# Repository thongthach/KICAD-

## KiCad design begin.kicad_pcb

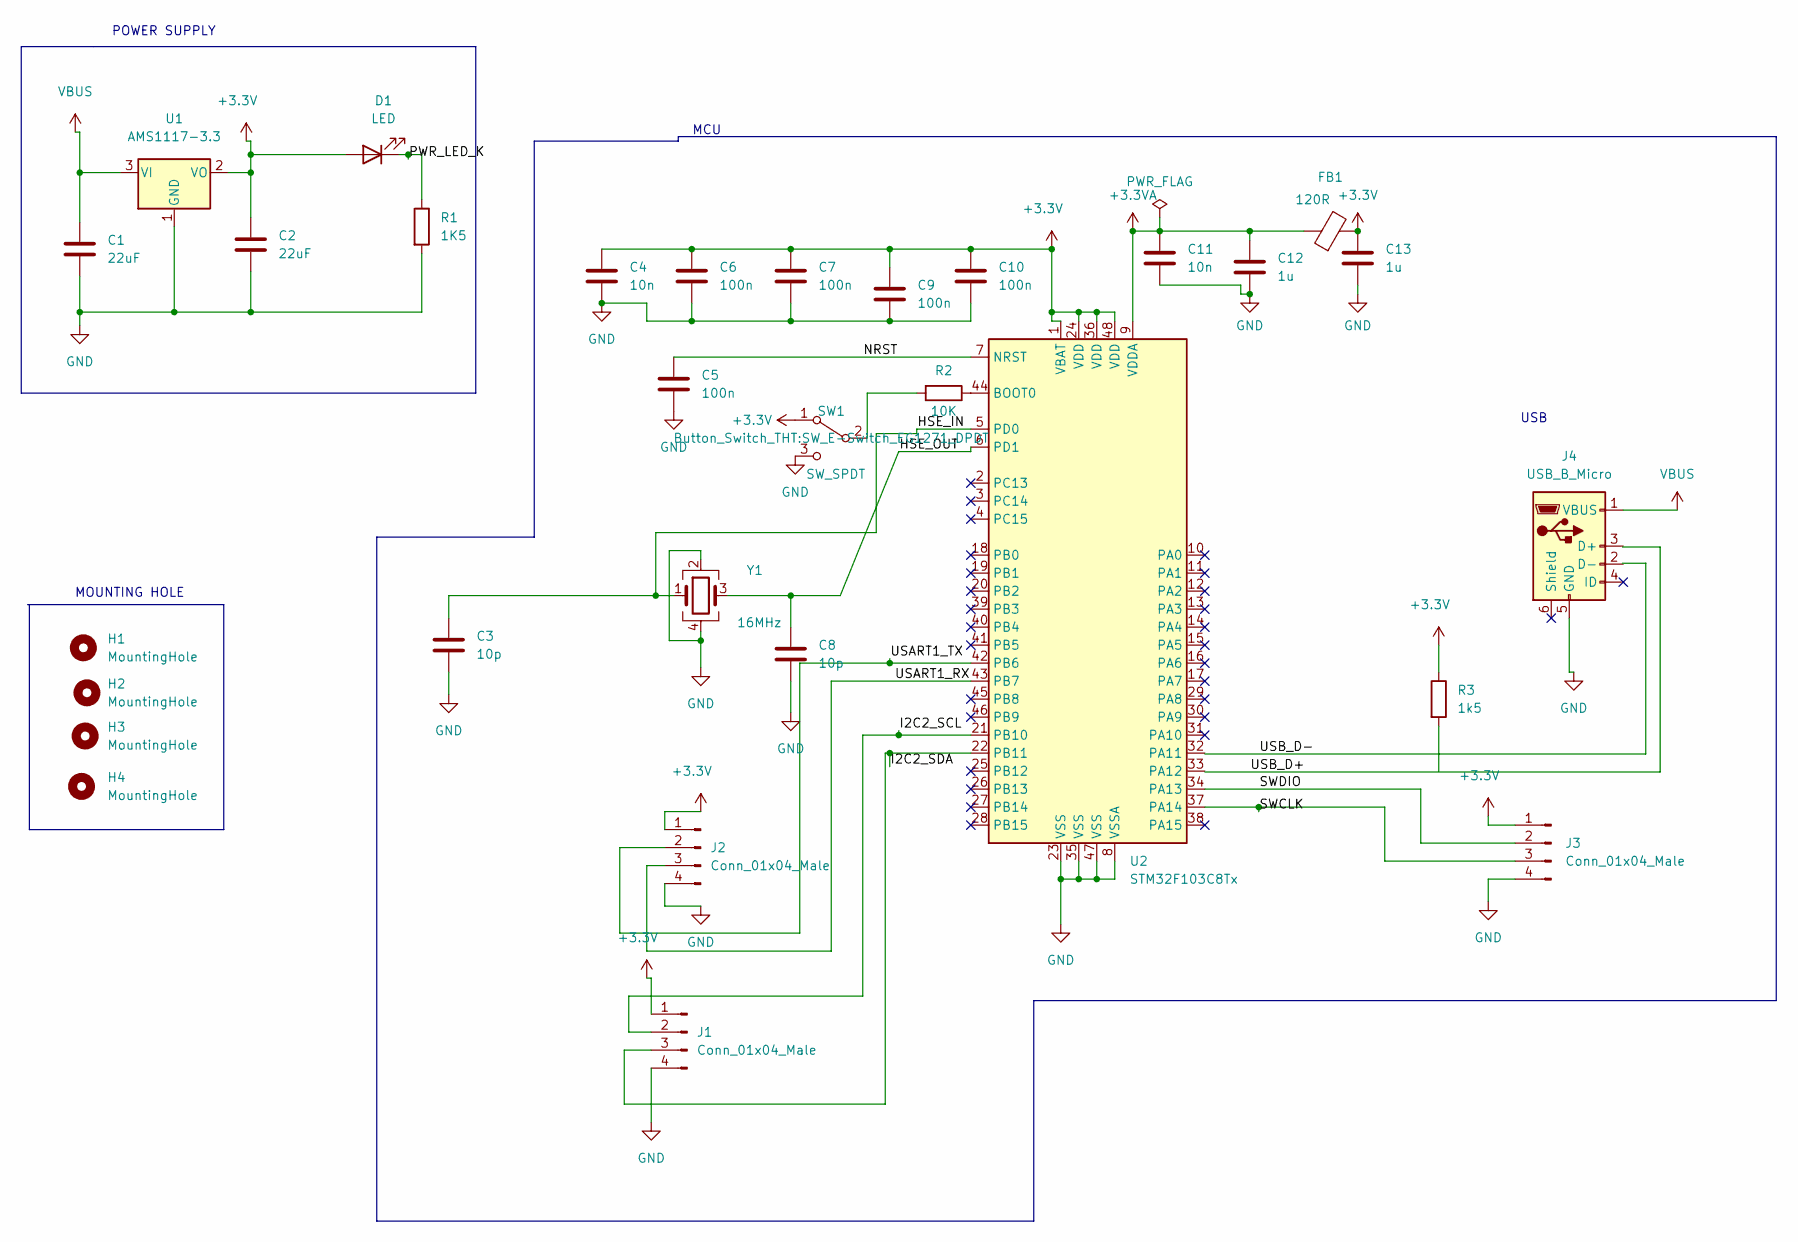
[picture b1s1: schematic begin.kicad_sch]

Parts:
C1, C2: 22uF; C_0805_2012Metric_Pad1.18x1.45mm_HandSolder
C3: 10p; C_0603_1608Metric_Pad1.08x0.95mm_HandSolder
C4: 10n; C_0603_1608Metric_Pad1.08x0.95mm_HandSolder
C5, C6, C7, C9, C10: 100n; C_0402_1005Metric
C8: 10p; C_0402_1005Metric
C11: 10n; C_0402_1005Metric
C12, C13: 1u; C_0402_1005Metric
D1: LED; LED_0603_1608Metric
FB1: 120R; L_0201_0603Metric
H1, H2, H3, H4: MountingHole; MountingHole_2.2mm_M2
J1, J2, J3: Conn_01x04_Male; PinHeader_1x04_P2.00mm_Vertical
J4: USB_B_Micro; USB_Micro-B_Wuerth_629105150521
R1: 1K5; R_0402_1005Metric
R2: 10K; R_0402_1005Metric
R3: 1k5; R_0402_1005Metric
SW1: SW_SPDT; SW_E-Switch_EG1271_DPDT
U1: AMS1117-3.3; SOT-223-3_TabPin2
U2: STM32F103C8Tx; LQFP-48_7x7mm_P0.5mm
Y1: 16MHz; Crystal_SMD_3225-4Pin_3.2x2.5mm

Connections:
+3.3VA: C11.1, C12.1, FB1.1, U2.9 (VDDA)
+3V3: C2.1, C4.1, C6.1, C7.1, C9.1, C10.1, C13.1, D1.2 (A), FB1.2, J1.1, J2.1, J3.1, R3.1, SW1.1 (A), U1.2 (VO), U2.1 (VBAT), U2.24 (VDD), U2.36 (VDD), U2.48 (VDD)
/HSE_IN: C3.1, U2.5 (PD0), Y1.1
/HSE_OUT: C8.1, U2.6 (PD1), Y1.3
/I2C2_SCL: J1.2, U2.21 (PB10)
/I2C2_SDA: J1.3, U2.22 (PB11)
/NRST: C5.1, U2.7 (NRST)
/PWR_LED_K: D1.1 (K), R1.1
/SWCLK: J3.3, U2.37 (PA14)
/SWDIO: J3.2, U2.34 (PA13)
/USART1_RX: J2.3, U2.43 (PB7)
/USART1_TX: J2.2, U2.42 (PB6)
/USB_D+: J4.2 (D-), R3.2, U2.33 (PA12)
/USB_D-: J4.3 (D+), U2.32 (PA11)
GND: C1.2, C2.2, C3.2, C4.2, C5.2, C6.2, C7.2, C8.2, C9.2, C10.2, C11.2, C12.2, C13.2, J1.4, J2.4, J3.4, J4.5 (GND), R1.2, SW1.3 (C), U1.1 (GND), U2.8 (VSSA), U2.23 (VSS), U2.35 (VSS), U2.47 (VSS), Y1.2, Y1.4
unnamed: R2.1, U2.44 (BOOT0)
unnamed: R2.2, SW1.2 (B)
VBUS: C1.1, J4.1 (VBUS), U1.3 (VI)

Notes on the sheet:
MCU
USB
POWER SUPPLY
MOUNTING HOLE

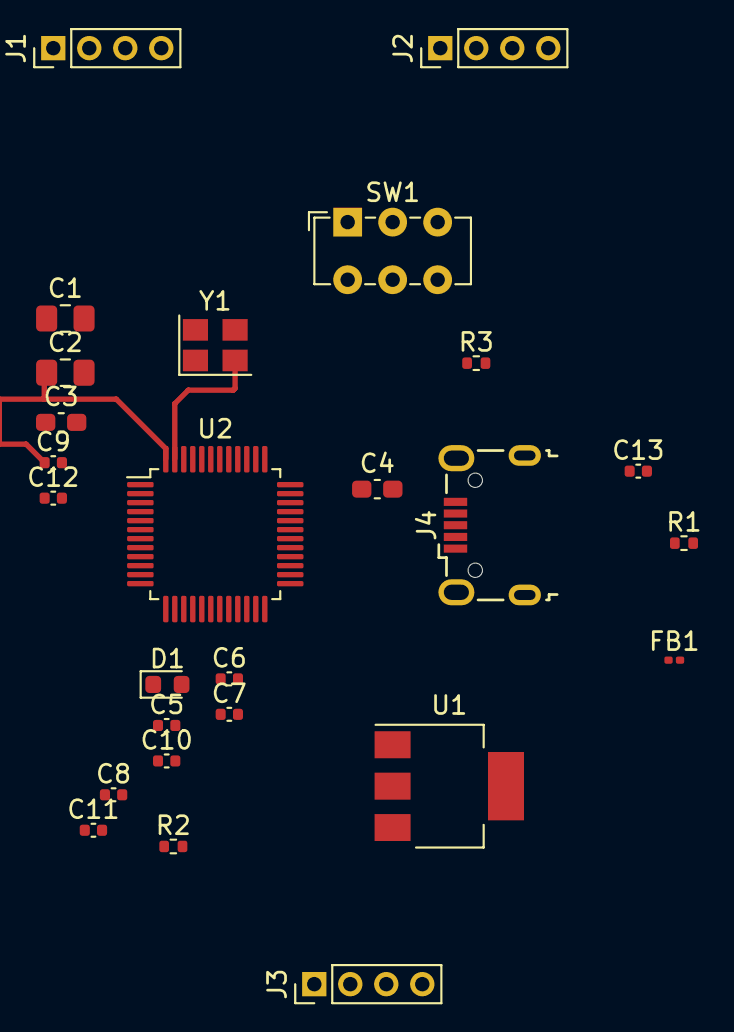
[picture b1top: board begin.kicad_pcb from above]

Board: 2 copper layers, 30 parts (0 on the bottom side), 18 nets.

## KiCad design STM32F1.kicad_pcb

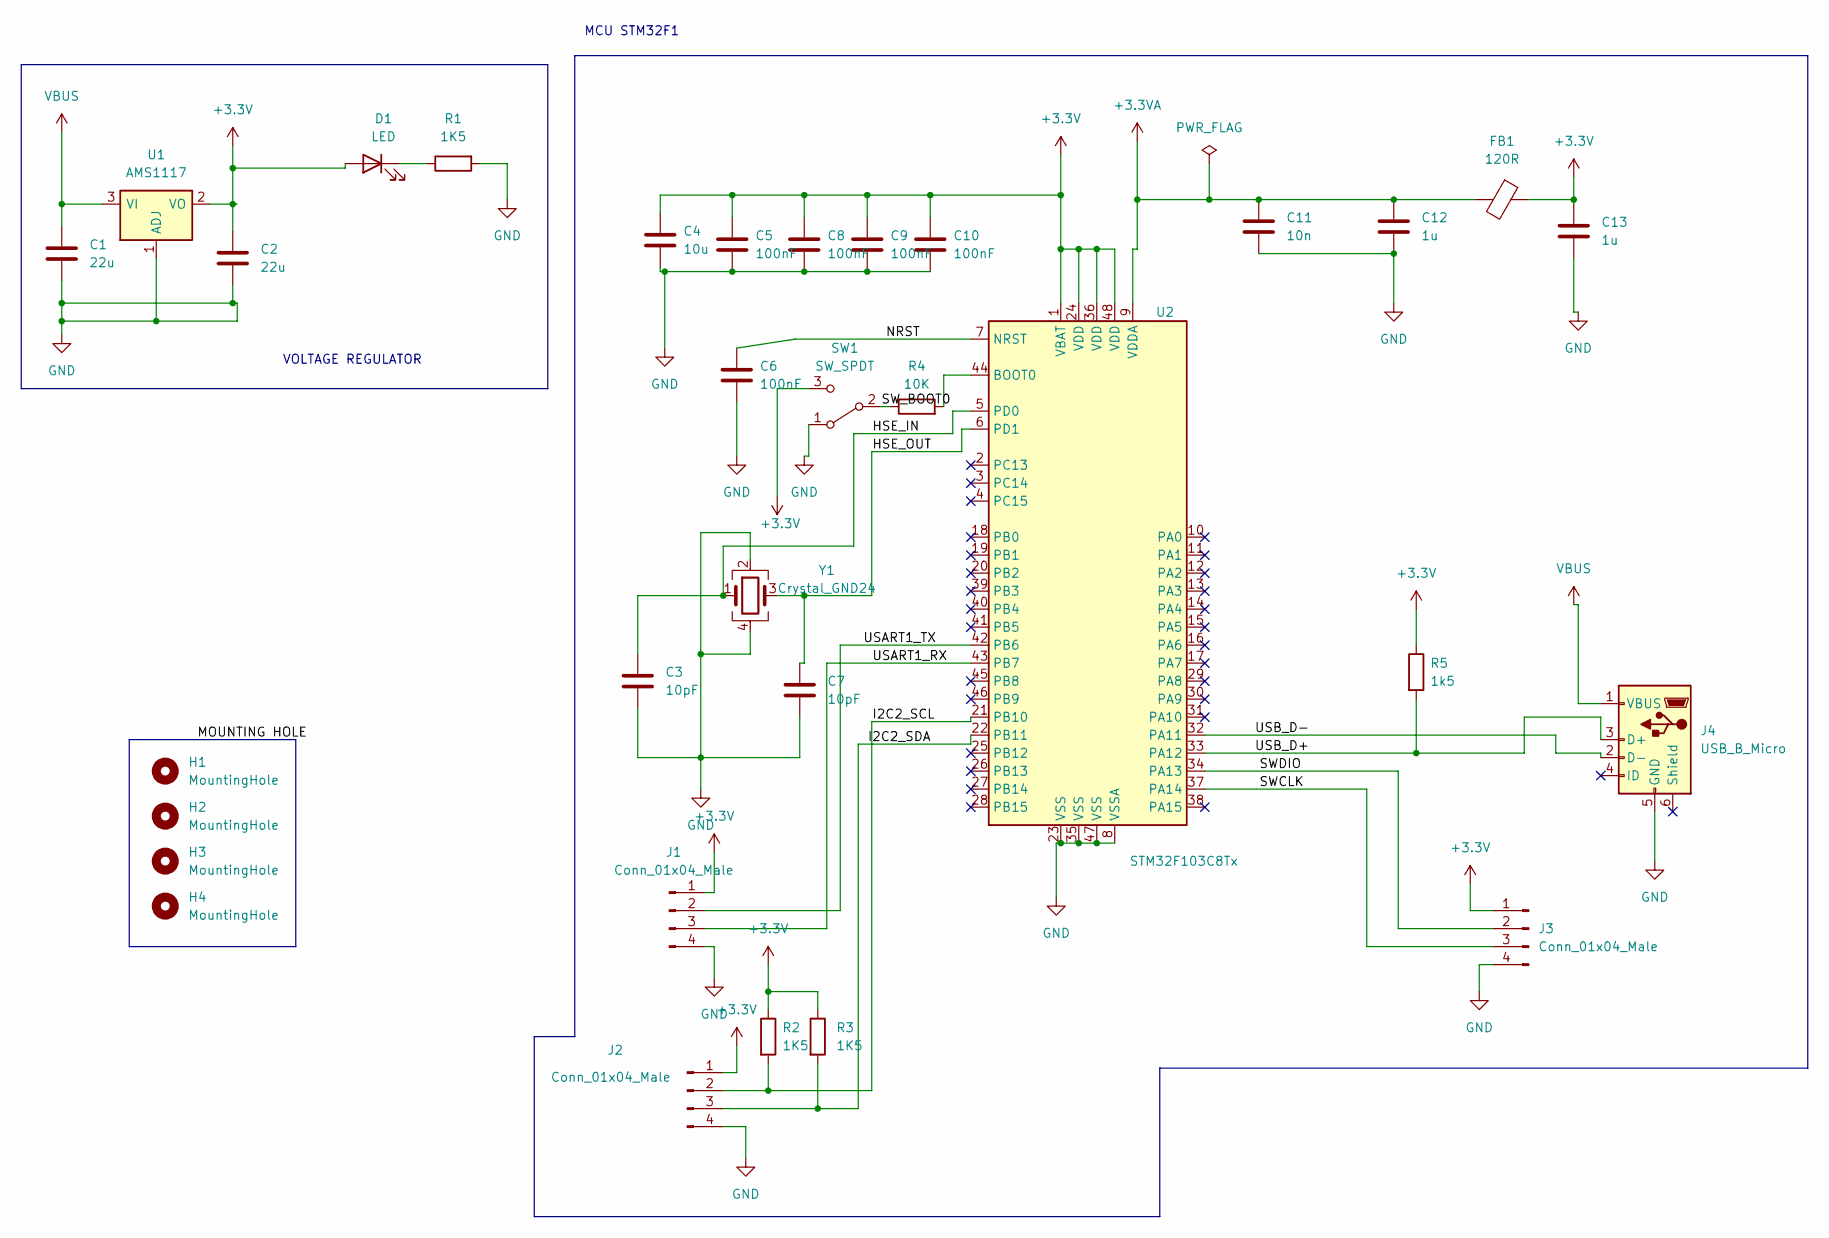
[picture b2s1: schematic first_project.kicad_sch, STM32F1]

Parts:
C1, C2: 22u; C_0805_2012Metric
C3, C7: 10pF; C_0402_1005Metric
C4: 10u; C_0603_1608Metric
C5, C6, C8, C9, C10: 100nF; C_0402_1005Metric
C11: 10n; C_0402_1005Metric
C12, C13: 1u; C_0402_1005Metric
D1: LED; LED_0603_1608Metric
FB1: 120R; L_0603_1608Metric
H1, H2, H3, H4: MountingHole; MountingHole_2.2mm_M2
J1, J2, J3: Conn_01x04_Male; PinHeader_1x04_P2.54mm_Vertical
J4: USB_B_Micro; USB_Micro-B_Wuerth_629105150521
R1, R2, R3: 1K5; R_0402_1005Metric
R4: 10K; R_0402_1005Metric
R5: 1k5; R_0402_1005Metric
SW1: SW_SPDT; SW_SPDT_PCM12
U1: AMS1117; SOT-223-3_TabPin2
U2: STM32F103C8Tx; LQFP-48_7x7mm_P0.5mm
Y1: Crystal_GND24; Crystal_SMD_3225-4Pin_3.2x2.5mm

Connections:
+3.3VA: C11.1, C12.1, FB1.2, U2.9 (VDDA)
+3V3: C2.1, C4.1, C5.1, C8.1, C9.1, C10.1, C13.1, D1.2 (A), FB1.1, J1.1, J2.1, J3.1, R2.1, R3.1, R5.1, SW1.3 (C), U1.2 (VO), U2.1 (VBAT), U2.24 (VDD), U2.36 (VDD), U2.48 (VDD)
/HSE_IN: C3.1, U2.5 (PD0), Y1.1
/HSE_OUT: C7.1, U2.6 (PD1), Y1.3
/I2C2_SCL: J2.2, R2.2, U2.21 (PB10)
/I2C2_SDA: J2.3, R3.2, U2.22 (PB11)
/NRST: C6.1, U2.7 (NRST)
/SWCLK: J3.3, U2.37 (PA14)
/SWDIO: J3.2, U2.34 (PA13)
/SW_BOOT0: R4.1, SW1.2 (B)
/USART1_RX: J1.3, U2.43 (PB7)
/USART1_TX: J1.2, U2.42 (PB6)
/USB_D+: J4.3 (D+), R5.2, U2.33 (PA12)
/USB_D-: J4.2 (D-), U2.32 (PA11)
GND: C1.2, C2.2, C3.2, C4.2, C5.2, C6.2, C7.2, C8.2, C9.2, C10.2, C11.2, C12.2, C13.2, J1.4, J2.4, J3.4, J4.5 (GND), R1.2, SW1.1 (A), U1.1 (ADJ), U2.8 (VSSA), U2.23 (VSS), U2.35 (VSS), U2.47 (VSS), Y1.2, Y1.4
unnamed: D1.1 (K), R1.1
unnamed: R4.2, U2.44 (BOOT0)
VBUS: C1.1, J4.1 (VBUS), U1.3 (VI)

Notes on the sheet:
VOLTAGE REGULATOR
MCU STM32F1

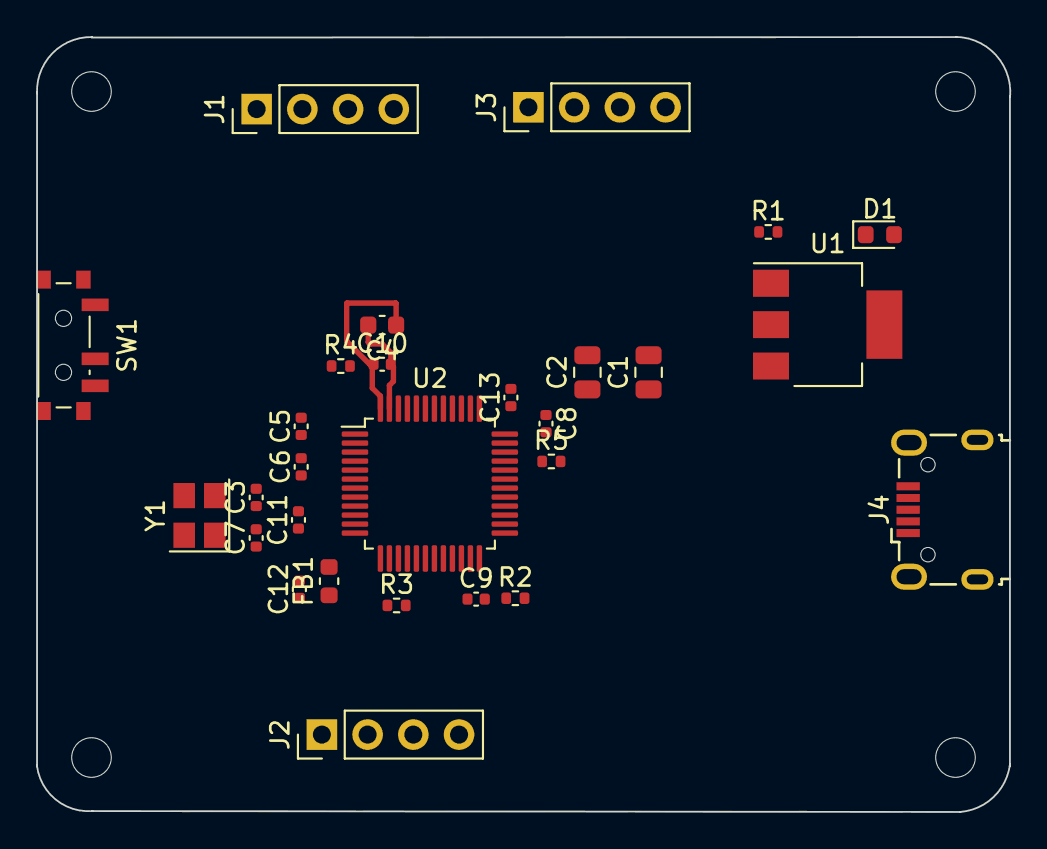
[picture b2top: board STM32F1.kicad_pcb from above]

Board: 2 copper layers, 54.1 x 43.1 mm, 32 parts (0 on the bottom side), 18 nets.
